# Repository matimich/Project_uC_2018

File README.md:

# Project_uC_2018

The aim of the project is to design and construct position registration system, based on STM32F411VET6 microcontroller.
The device will be using following modules:

-GPS module
-microSD card driver
-GSM module

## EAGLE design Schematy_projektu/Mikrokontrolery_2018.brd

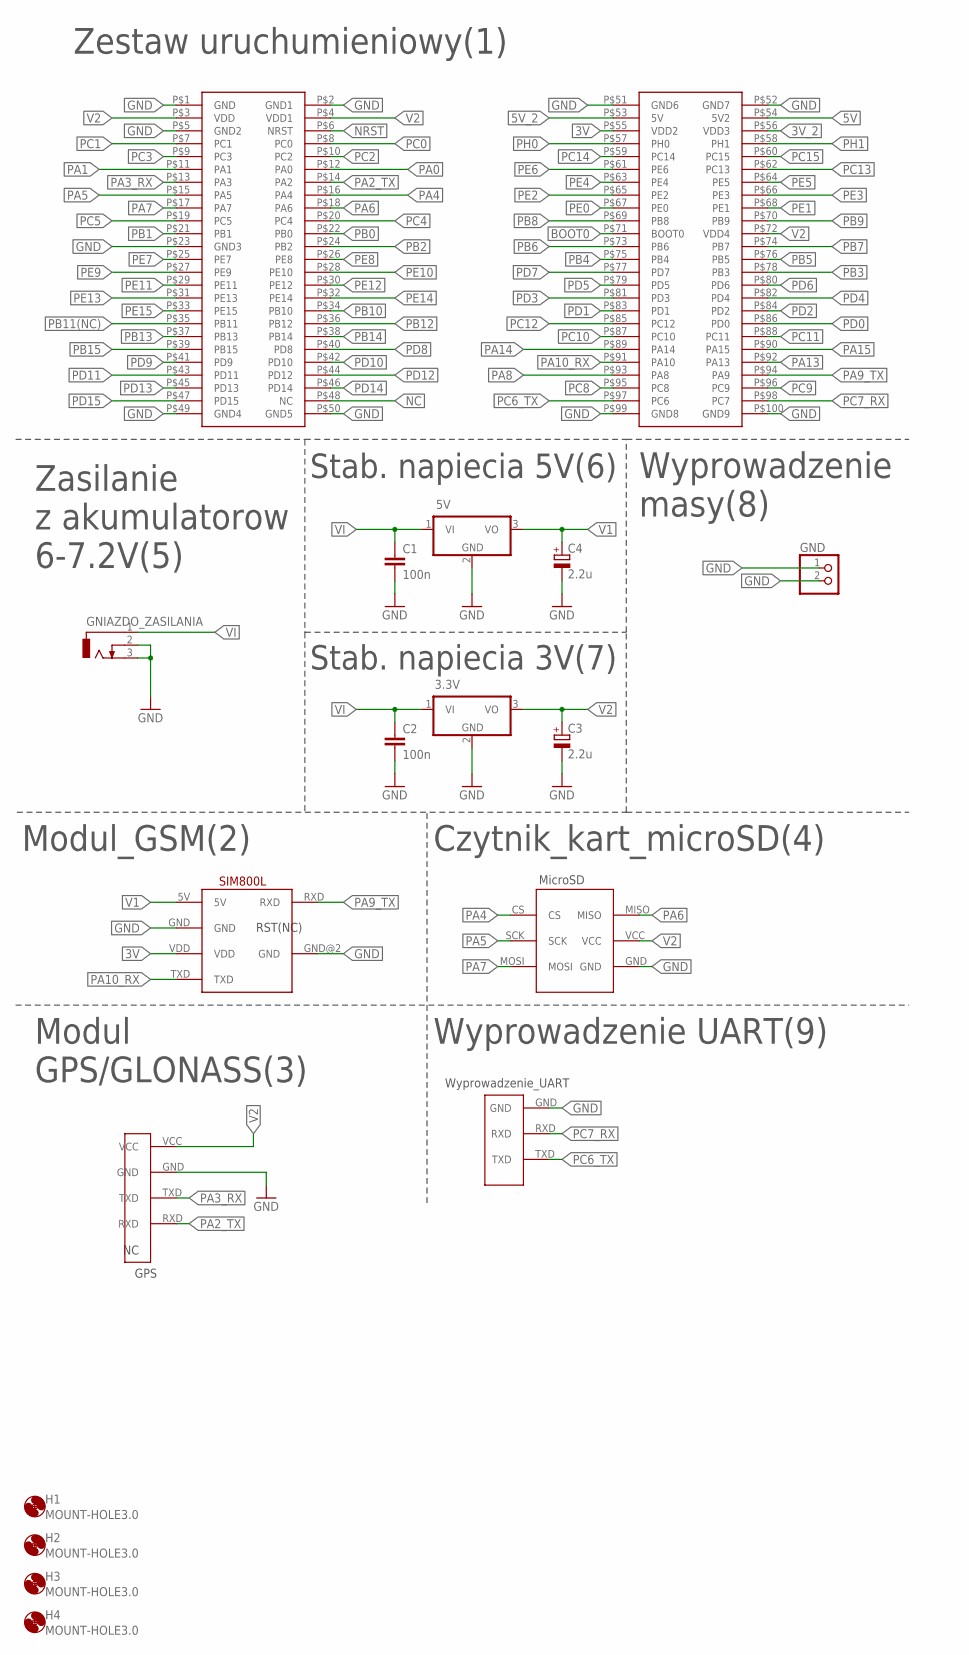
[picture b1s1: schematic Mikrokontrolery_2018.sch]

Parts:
3.3V, 5V: 7805TV; TO220V
C1, C2: 100n; C1206K
C3, C4: 2.2u; A/3216-18W
GND: PINHD-1X2; 1X02
GNIAZDO_ZASILANIA: WEJSCIE_VCC; DCJ0202
H1, H2, H3, H4: MOUNT-HOLE3.0; 3,0
U$1: MODUL_GPS
U$3: MODUL_GSM
U$4: STM32F4-DISCOVERY
U$5: WYPROWADZENIE_UART
U$6: MICROSD

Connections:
3V: U$3.VDD, U$4.P$55 (VDD2)
3V_2: U$4.P$56 (VDD3)
5V: U$4.P$54 (5V2)
5V_2: U$4.P$53 (5V)
BOOT0: U$4.P$71 (BOOT0)
GND: 3.3V.2 (GND), 5V.2 (GND), C1.2, C2.2, C3.-, C4.-, GND.1, GND.2, GNIAZDO_ZASILANIA.2, GNIAZDO_ZASILANIA.3, U$1.GND, U$3.GND, U$3.GND@2 (GND), U$4.P$1 (GND), U$4.P$2 (GND1), U$4.P$5 (GND2), U$4.P$23 (GND3), U$4.P$49 (GND4), U$4.P$50 (GND5), U$4.P$51 (GND6), U$4.P$52 (GND7), U$4.P$99 (GND8), U$4.P$100 (GND9), U$5.GND, U$6.GND
NC: U$4.P$48 (NC)
NRST: U$4.P$6 (NRST)
PA0: U$4.P$12 (PA0)
PA1: U$4.P$11 (PA1)
PA2_TX: U$1.RXD, U$4.P$14 (PA2)
PA3_RX: U$1.TXD, U$4.P$13 (PA3)
PA4: U$4.P$16 (PA4), U$6.CS
PA5: U$4.P$15 (PA5), U$6.SCK
PA6: U$4.P$18 (PA6), U$6.MISO
PA7: U$4.P$17 (PA7), U$6.MOSI
PA8: U$4.P$93 (PA8)
PA9_TX: U$3.RXD, U$4.P$94 (PA9)
PA10_RX: U$3.TXD, U$4.P$91 (PA10)
PA13: U$4.P$92 (PA13)
PA14: U$4.P$89 (PA14)
PA15: U$4.P$90 (PA15)
PB0: U$4.P$22 (PB0)
PB1: U$4.P$21 (PB1)
PB2: U$4.P$24 (PB2)
PB3: U$4.P$78 (PB3)
PB4: U$4.P$75 (PB4)
PB5: U$4.P$76 (PB5)
PB6: U$4.P$73 (PB6)
PB7: U$4.P$74 (PB7)
PB8: U$4.P$69 (PB8)
PB9: U$4.P$70 (PB9)
PB10: U$4.P$34 (PB10)
PB11(NC): U$4.P$35 (PB11)
PB12: U$4.P$36 (PB12)
PB13: U$4.P$37 (PB13)
PB14: U$4.P$38 (PB14)
PB15: U$4.P$39 (PB15)
PC0: U$4.P$8 (PC0)
PC1: U$4.P$7 (PC1)
PC2: U$4.P$10 (PC2)
PC3: U$4.P$9 (PC3)
PC4: U$4.P$20 (PC4)
PC5: U$4.P$19 (PC5)
PC6_TX: U$4.P$97 (PC6), U$5.TXD
PC7_RX: U$4.P$98 (PC7), U$5.RXD
PC8: U$4.P$95 (PC8)
PC9: U$4.P$96 (PC9)
PC10: U$4.P$87 (PC10)
PC11: U$4.P$88 (PC11)
PC12: U$4.P$85 (PC12)
PC13: U$4.P$62 (PC13)
PC14: U$4.P$59 (PC14)
PC15: U$4.P$60 (PC15)
PD0: U$4.P$86 (PD0)
PD1: U$4.P$83 (PD1)
PD2: U$4.P$84 (PD2)
PD3: U$4.P$81 (PD3)
PD4: U$4.P$82 (PD4)
PD5: U$4.P$79 (PD5)
PD6: U$4.P$80 (PD6)
PD7: U$4.P$77 (PD7)
PD8: U$4.P$40 (PD8)
PD9: U$4.P$41 (PD9)
PD10: U$4.P$42 (PD10)
PD11: U$4.P$43 (PD11)
PD12: U$4.P$44 (PD12)
PD13: U$4.P$45 (PD13)
PD14: U$4.P$46 (PD14)
PD15: U$4.P$47 (PD15)
PE0: U$4.P$67 (PE0)
PE1: U$4.P$68 (PE1)
PE2: U$4.P$65 (PE2)
PE3: U$4.P$66 (PE3)
PE4: U$4.P$63 (PE4)
PE5: U$4.P$64 (PE5)
PE6: U$4.P$61 (PE6)
PE7: U$4.P$25 (PE7)
PE8: U$4.P$26 (PE8)
PE9: U$4.P$27 (PE9)
PE10: U$4.P$28 (PE10)
PE11: U$4.P$29 (PE11)
PE12: U$4.P$30 (PE12)
PE13: U$4.P$31 (PE13)
PE14: U$4.P$32 (PE14)
PE15: U$4.P$33 (PE15)
PH0: U$4.P$57 (PH0)
PH1: U$4.P$58 (PH1)
V1: 5V.3 (VO), C4.+, U$3.5V
V2: 3.3V.3 (VO), C3.+, U$1.VCC, U$4.P$3 (VDD), U$4.P$4 (VDD1), U$4.P$72 (VDD4), U$6.VCC
VI: 3.3V.1 (VI), 5V.1 (VI), C1.1, C2.1, GNIAZDO_ZASILANIA.1

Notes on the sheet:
Zestaw uruchumieniowy(1)
Zasilanie z akumulatorow 6-7.2V(5)
Modul GPS/GLONASS(3)
Modul_GSM(2)
Czytnik_kart_microSD(4)
Wyprowadzenie UART(9)
Wyprowadzenie masy(8)
Stab. napiecia 5V(6)
Stab. napiecia 3V(7)

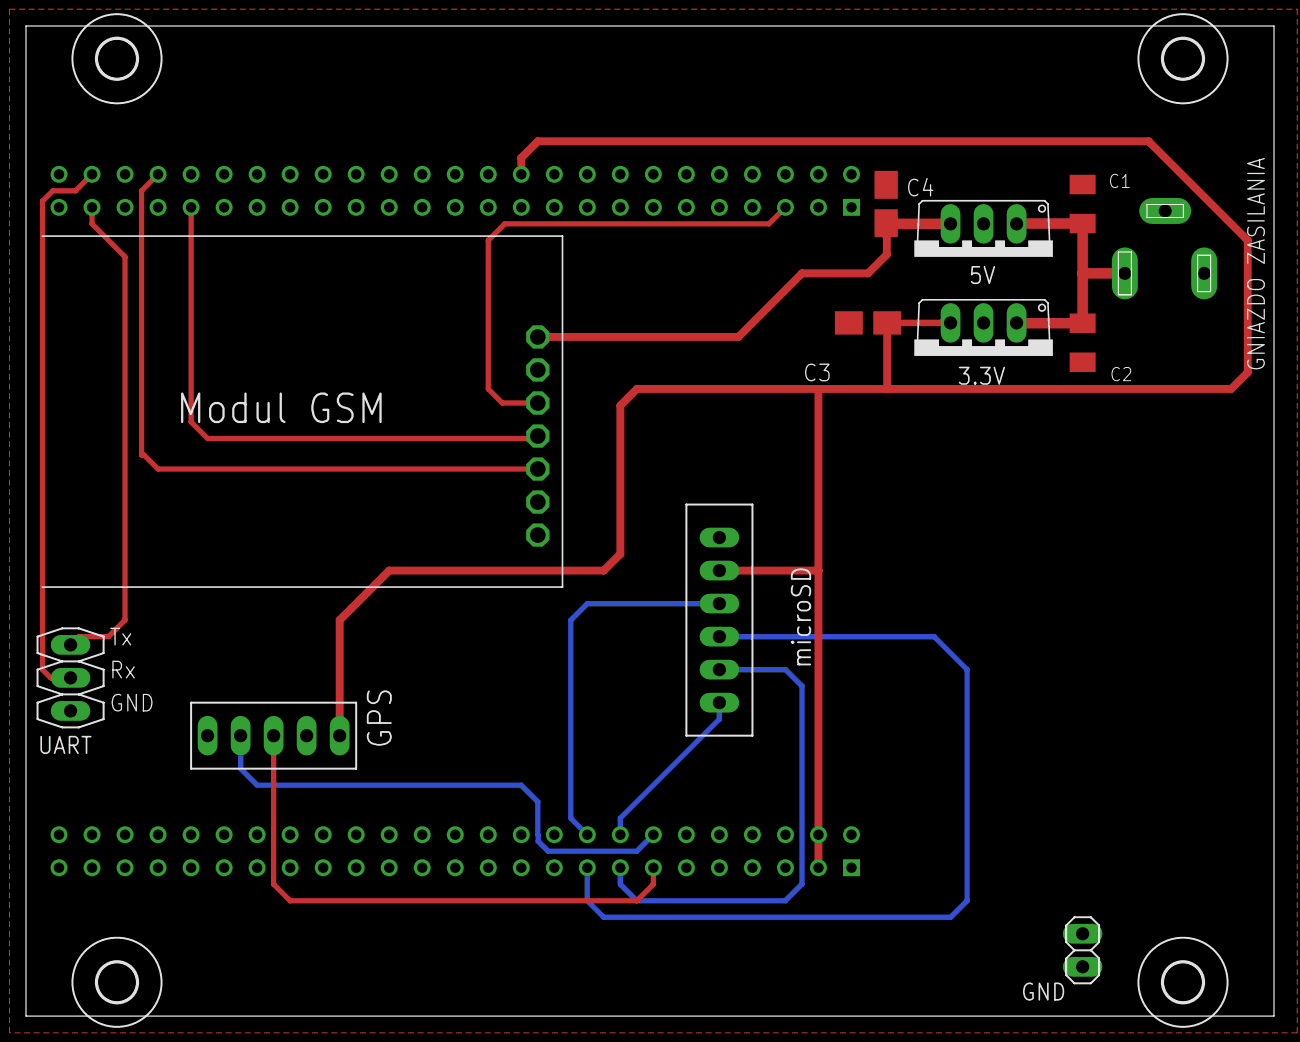
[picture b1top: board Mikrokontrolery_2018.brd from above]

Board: 2 copper layers, 96.0 x 76.2 mm, 17 parts (1 on the bottom side), 15 nets.

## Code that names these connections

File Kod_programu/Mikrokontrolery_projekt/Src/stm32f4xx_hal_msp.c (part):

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  
    __HAL_RCC_GPIOA_CLK_ENABLE();
    /**SPI1 GPIO Configuration    
    PA4     ------> SPI1_NSS
    PA5     ------> SPI1_SCK
    PA6     ------> SPI1_MISO
    PA7     ------> SPI1_MOSI 
    */
    GPIO_InitStruct.Pin = GPIO_PIN_4|GPIO_PIN_5|GPIO_PIN_6|GPIO_PIN_7;
    GPIO_InitStruct.Mode = GPIO_MODE_AF_PP;
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    __HAL_RCC_SPI1_CLK_DISABLE();
  
    /**SPI1 GPIO Configuration    
    PA4     ------> SPI1_NSS
    PA5     ------> SPI1_SCK
    PA6     ------> SPI1_MISO
    PA7     ------> SPI1_MOSI 
    */
    HAL_GPIO_DeInit(GPIOA, GPIO_PIN_4|GPIO_PIN_5|GPIO_PIN_6|GPIO_PIN_7);

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  
    __HAL_RCC_GPIOA_CLK_ENABLE();
    /**USART2 GPIO Configuration    
    PA2     ------> USART2_TX
    PA3     ------> USART2_RX 
    */
    GPIO_InitStruct.Pin = GPIO_PIN_2|GPIO_PIN_3;
    GPIO_InitStruct.Mode = GPIO_MODE_AF_PP;
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  
    __HAL_RCC_GPIOC_CLK_ENABLE();
    /**USART6 GPIO Configuration    
    PC6     ------> USART6_TX
    PC7     ------> USART6_RX 
    */
    GPIO_InitStruct.Pin = GPIO_PIN_6|GPIO_PIN_7;
    GPIO_InitStruct.Mode = GPIO_MODE_AF_PP;
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    __HAL_RCC_USART2_CLK_DISABLE();
  
    /**USART2 GPIO Configuration    
    PA2     ------> USART2_TX
    PA3     ------> USART2_RX 
    */
    HAL_GPIO_DeInit(GPIOA, GPIO_PIN_2|GPIO_PIN_3);

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    __HAL_RCC_USART6_CLK_DISABLE();
  
    /**USART6 GPIO Configuration    
    PC6     ------> USART6_TX
    PC7     ------> USART6_RX 
    */
    HAL_GPIO_DeInit(GPIOC, GPIO_PIN_6|GPIO_PIN_7);

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
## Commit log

2018-10-15 Rename README.md to README.txt
2018-10-15 Dodanie schematy blokowego
2018-10-15 Dodanie schematu blokowego
2018-10-15 Dodanie nowych folderow
2018-10-15 Poprawa schematu, dodanie elementów
2018-10-15 Poprawka Gantt
2018-10-22 22.10.2018
2018-10-29 30.10.2018
2018-11-09 0.9.11.2018
2018-11-10 10.11.2018
2018-11-27 27.11.2018
2018-12-09 09.12.2018
2018-12-10 10.12.2018
2019-01-06 06.01.2019
2019-01-26 26.01.2019
2019-01-28 28.01.2019

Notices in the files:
Kod_programu/Mikrokontrolery_projekt/Src/stm32f4xx_hal_msp.c:
Copyright (c) 2019 STMicroelectronics International N.V.
All rights reserved.
(C) COPYRIGHT STMicroelectronics *****END OF FILE
